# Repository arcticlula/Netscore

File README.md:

# Netscore
Device that keeps track of a volleyball's game score (points and sets). 

Ideally it should be mounted on the net, since it has a display on the front and back and buttons on the sides.

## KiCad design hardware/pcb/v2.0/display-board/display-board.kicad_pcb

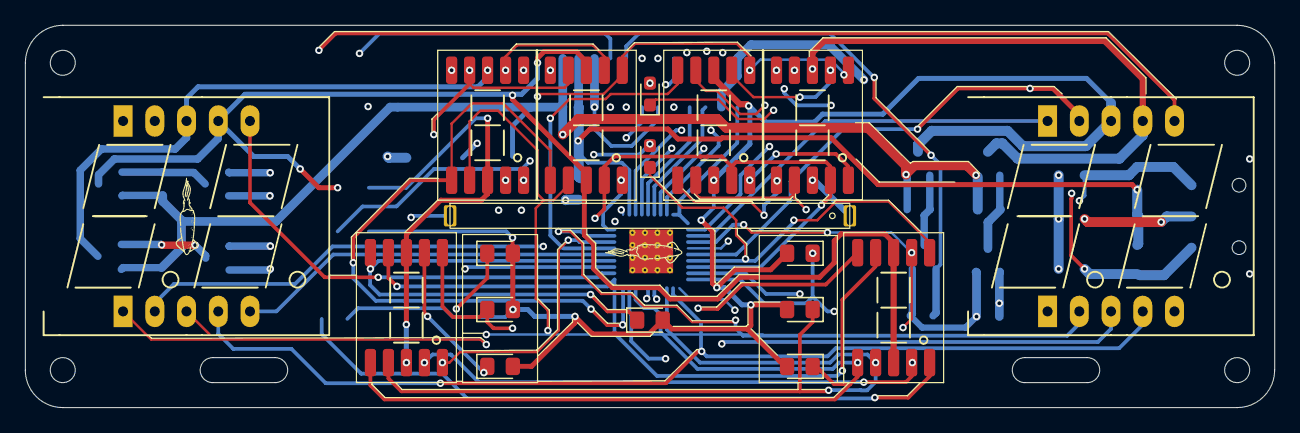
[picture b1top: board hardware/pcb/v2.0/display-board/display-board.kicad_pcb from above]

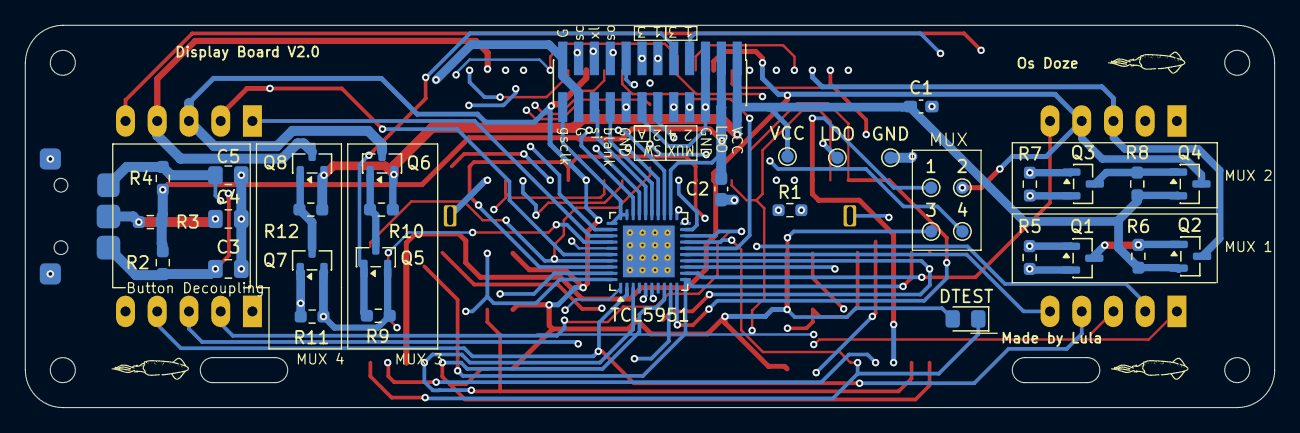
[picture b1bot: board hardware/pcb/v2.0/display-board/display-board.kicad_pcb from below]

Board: 4 copper layers, 100.0 x 30.6 mm, 58 parts (36 on the bottom side), 51 nets.

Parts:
1, 2, 3, 4: TestPoint; TestPoint_Pad_D1.0mm
A1: Conn_02x12_Odd_Even; PinHeader_2x12_P1.27mm_Vertical_SMD
C1: 10uF; C_0603_1608Metric_Pad1.08x0.95mm_HandSolder
C2: 0.1uF; C_0603_1608Metric_Pad1.08x0.95mm_HandSolder
C3, C4, C5: 2.2uF; C_0805_2012Metric_Pad1.18x1.45mm_HandSolder
D1: LED; LED Bar
D3, D4, D5, D6, D7, D8, D9: LED; LED_0805_2012Metric_Pad1.15x1.40mm_HandSolder
D10, D11: LED; LED_0603_1608Metric_Pad1.05x0.95mm_HandSolder
DTEST: LED; LED_0805_2012Metric_Pad1.15x1.40mm_HandSolder
GND: TestPoint; TestPoint_Pad_D1.0mm
H1, H2, H3, H4: MountingHole; MountingHole_2mm
LDO: TestPoint; TestPoint_Pad_D1.0mm
Q1, Q3, Q5, Q7: AO3400A; SOT-23
Q2, Q4, Q6, Q8: AO3401A; SOT-23
R1: 651; R_0603_1608Metric_Pad0.98x0.95mm_HandSolder
R2, R3, R4: 100k; R_0603_1608Metric_Pad0.98x0.95mm_HandSolder
R5, R6, R7, R8, R9, R10, R11, R12: 10K; R_0603_1608Metric_Pad0.98x0.95mm_HandSolder
SW1: Thumbwheel
TCL5951: TLC5951RHA; Texas_RHA0040B_VQFN-40-1EP_6x6mm_P0.5mm_EP4.15x4.15mm_Therm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
U2, U4, U5, U6, U7, U9: GS-S2011AB; GS-2011AB
U3, U8: 7Seg 2Dig 0.56in; 7Seg 0.56In Double
VCC: TestPoint; TestPoint_Pad_D1.0mm

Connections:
/7SEG_MUX_1: 1.1, Q2.3 (D), U2.3 (CA), U2.8 (CA), U3.8 (CA_D1), U4.3 (CA), U4.8 (CA)
/7SEG_MUX_2: 2.1, Q4.3 (D), U3.7 (CA_D2), U5.3 (CA), U5.8 (CA), U6.3 (CA), U6.8 (CA)
/7SEG_MUX_3: 3.1, D3.2 (A), D4.2 (A), D5.2 (A), D6.2 (A), D7.2 (A), D8.2 (A), D9.2 (A), DTEST.2 (A), Q6.3 (D), U7.3 (CA), U7.8 (CA), U8.8 (CA_D1)
/7SEG_MUX_4: 4.1, D1.2 (A), D10.2 (A), D11.2 (A), Q8.3 (D), U8.7 (CA_D2), U9.3 (CA), U9.8 (CA)
/BLANK: A1.17, TCL5951.23 (XBLNK)
/DCSIN: A1.18, TCL5951.25 (DCSIN)
/DCSOUT: A1.16, TCL5951.6 (DCSOUT)
/GSCLK: A1.24, TCL5951.29 (GSCKG), TCL5951.30 (GSCKR), TCL5951.31 (GSCKB)
/GSLAT: A1.19, TCL5951.28 (GSLAT)
/GSSIN: A1.20, TCL5951.26 (GSSIN)
/GSSOUT: A1.15, TCL5951.5 (GSSOUT)
/LDO_CTRL: A1.3, A1.4, C2.1, LDO.1, R2.1, R3.1, R4.1, TCL5951.22 (VCC)
/MUX_1: A1.7, Q1.1 (G), R5.1
/MUX_2: A1.8, Q3.1 (G), R7.1
/MUX_3: A1.9, Q5.1 (G), R9.1
/MUX_4: A1.10, Q7.1 (G), R11.1
/OUTB0: D5.1 (K), D10.1 (K), TCL5951.34 (OUTB0), U4.7 (A), U6.7 (A)
/OUTB1: D4.1 (K), D11.1 (K), TCL5951.37 (OUTB1), U4.6 (B), U6.6 (B)
/OUTB2: D1.1 (K), D7.1 (K), TCL5951.40 (OUTB2), U4.4 (C), U6.4 (C)
/OUTB3: D8.1 (K), TCL5951.3 (OUTB3), U4.2 (D), U6.2 (D)
/OUTB4: D9.1 (K), TCL5951.8 (OUTB4), U4.1 (E), U6.1 (E)
/OUTB5: D3.1 (K), TCL5951.11 (OUTB5), U4.9 (F), U6.9 (F)
/OUTB6: D6.1 (K), TCL5951.14 (OUTB6), U4.10 (G), U6.10 (G)
/OUTB7: DTEST.1 (K), TCL5951.17 (OUTB7), U4.5 (DP), U6.5 (DP)
/OUTG0: TCL5951.32 (OUTG0), U2.7 (A), U5.7 (A), U7.7 (A), U9.7 (A)
/OUTG1: TCL5951.35 (OUTG1), U2.6 (B), U5.6 (B), U7.6 (B), U9.6 (B)
/OUTG2: TCL5951.38 (OUTG2), U2.4 (C), U5.4 (C), U7.4 (C), U9.4 (C)
/OUTG3: TCL5951.1 (OUTG3), U2.2 (D), U5.2 (D), U7.2 (D), U9.2 (D)
/OUTG4: TCL5951.10 (OUTG4), U2.1 (E), U5.1 (E), U7.1 (E), U9.1 (E)
/OUTG5: TCL5951.13 (OUTG5), U2.9 (F), U5.9 (F), U7.9 (F), U9.9 (F)
/OUTG6: TCL5951.16 (OUTG6), U2.10 (G), U5.10 (G), U7.10 (G), U9.10 (G)
/OUTG7: TCL5951.19 (OUTG7), U2.5 (DP), U5.5 (DP), U7.5 (DP), U9.5 (DP)
/OUTR0: TCL5951.33 (OUTR0), U3.10 (a), U8.10 (a)
/OUTR1: TCL5951.36 (OUTR1), U3.9 (b), U8.9 (b)
/OUTR2: TCL5951.39 (OUTR2), U3.1 (c), U8.1 (c)
/OUTR3: TCL5951.2 (OUTR3), U3.4 (d), U8.4 (d)
/OUTR4: TCL5951.9 (OUTR4), U3.3 (e), U8.3 (e)
/OUTR5: TCL5951.12 (OUTR5), U3.6 (f), U8.6 (f)
/OUTR6: TCL5951.15 (OUTR6), U3.5 (g), U8.5 (g)
/OUTR7: TCL5951.18 (OUTR7), U3.2 (DP), U8.2 (DP)
/SCLK: A1.21, TCL5951.24 (DCSCK), TCL5951.27 (GSSCK)
/SW_1: A1.11, C3.1, R2.2, SW1.1
/SW_2: A1.12, C4.1, R3.2, SW1.T
/SW_3: A1.13, C5.1, R4.2, SW1.2
/VCC_CTRL: A1.1, A1.2, C1.1, Q2.2 (S), Q4.2 (S), Q6.2 (S), Q8.2 (S), R6.1, R8.1, R10.1, R12.1, VCC.1
GND: A1.5, A1.6, A1.14, A1.22, A1.23, C1.2, C2.2, C3.2, C4.2, C5.2, GND.1, Q1.2 (S), Q3.2 (S), Q5.2 (S), Q7.2 (S), R1.2, R5.2, R7.2, R9.2, R11.2, SW1.C, TCL5951.20 (GND), TCL5951.41 (GND)
unnamed: Q1.3 (D), Q2.1 (G), R6.2
unnamed: Q3.3 (D), Q4.1 (G), R8.2
unnamed: Q5.3 (D), Q6.1 (G), R10.2
unnamed: Q7.3 (D), Q8.1 (G), R12.2
unnamed: R1.1, TCL5951.21 (IREF)

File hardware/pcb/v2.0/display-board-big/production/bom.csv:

Designator,Footprint,Quantity,Value,LCSC Part #
"1, 2, 3, 4, GND, LDO, VCC",TestPoint_Pad_D1.0mm,7,TestPoint,
A1,PinHeader_2x12_P1.27mm_Vertical_SMD,1,Conn_02x12_Odd_Even,
C1,0603,1,10uF,
C2,0603,1,0.1uF,
"C3, C4, C5",0805,3,2.2uF,
"D1, D13, D14, D6",LED Bar,4,BAR LED,
"D10, D3, D4, D5, D7, D8, D9, DT1, DT2, DT3",0805,10,LED,
"D11, D12",0603,2,LED,
"Q1, Q3, Q5, Q7",SOT-23,4,AO3400A,
"Q2, Q4, Q6, Q8",SOT-23,4,AO3401A,
R1,0603,1,651,
"R10, R11, R12, R5, R6, R7, R8, R9",0603,8,10K,
"R2, R3, R4",0603,3,100k,
SW1,Thumbwheel,1,~,
U1,Texas_RHA0040B_VQFN-40-1EP_6x6mm_P0.5mm_EP4.15x4.15mm_ThermalVias,1,TLC5951RHA,
"U10, U3, U5, U6, U7, U8",GS-2011AB,6,GS-S2011AB,
"U11, U2, U4, U9",7Seg SMD 0.8in Single,4,SMD 0.8in,

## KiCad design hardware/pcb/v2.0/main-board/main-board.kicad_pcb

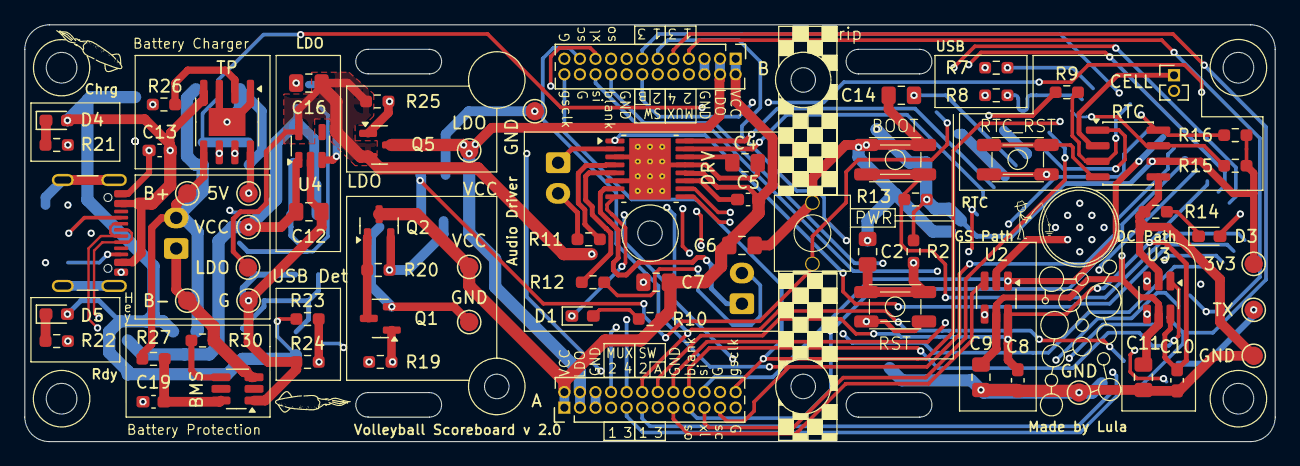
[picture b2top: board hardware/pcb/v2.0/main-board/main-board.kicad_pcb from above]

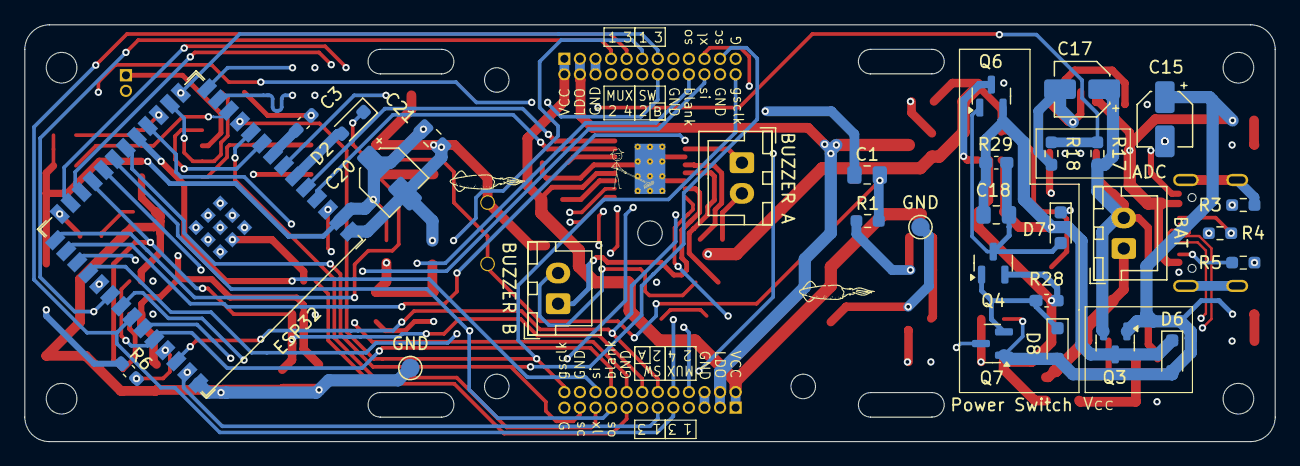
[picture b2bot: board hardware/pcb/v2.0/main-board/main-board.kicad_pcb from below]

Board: 4 copper layers, 102.0 x 34.0 mm, 109 parts (30 on the bottom side), 80 nets.

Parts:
3v3, 5V: TestPoint_Alt; TestPoint_Pad_D1.5mm
A: Conn_02x12_Odd_Even; PinHeader_2x12_P1.27mm_Vertical
B: Conn_02x12_Odd_Even; PinHeader_2x12_P1.27mm_Vertical
B+: TestPoint_Alt; TestPoint_Pad_D1.5mm
B-: TestPoint_Alt; TestPoint_Pad_D1.5mm
BAT: Conn_01x02_Pin; JST_XH_B2B-XH-A_1x02_P2.50mm_Vertical
BMS: FS312MH; SOT-23-6_Handsoldering
BOOT: SW_Push; Button_3x4x2.5
BUZZER A: Conn_01x02_Pin; JST_XH_B2B-XH-A_1x02_P2.50mm_Vertical
BUZZER B: Conn_01x02_Pin; JST_XH_B2B-XH-A_1x02_P2.50mm_Vertical
C1, C2: 100nF; C_0805_2012Metric_Pad1.18x1.45mm_HandSolder
C3, C8, C10: 1nF; C_0603_1608Metric_Pad1.08x0.95mm_HandSolder
C4: 2.2uF; C_0805_2012Metric_Pad1.18x1.45mm_HandSolder
C5: 10nF; C_0603_1608Metric_Pad1.08x0.95mm_HandSolder
C6: 10uF; C_0805_2012Metric_Pad1.18x1.45mm_HandSolder
C7, C9, C11, C14, C18, C21: 0.1uF; C_0805_2012Metric_Pad1.18x1.45mm_HandSolder
C12, C16: 1uF; C_0805_2012Metric_Pad1.18x1.45mm_HandSolder
C13, C19: 100nF; C_0603_1608Metric_Pad1.08x0.95mm_HandSolder
C15, C17, C20: 10uF; CP_Elec_4x5.3
CELL: Conn_01x02_Pin; PinHeader_1x02_P1.27mm_Vertical
D1, D3, D4, D5: LED; LED_0603_1608Metric_Pad1.05x0.95mm_HandSolder
D2, D6, D7, D8: BAT20J; D_SOD-323_HandSoldering
DRV: DRV8833PWP; HTSSOP-16-1EP_4.4x5mm_P0.65mm_EP3.4x5mm_Mask2.46x2.31mm_The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
ESP32: ESP32-S3-WROOM-1; ESP32-S3-WROOM-1U
G: TestPoint_Alt; TestPoint_Pad_D1.5mm
GND: TestPoint_Alt; TestPoint_Pad_D1.5mm
GND#2, GND#3, GND#4, GND#5, GND#6: TestPoint_Alt; TestPoint_Pad_D1.5mm
H1, H2, H3, H4, H5, H6, H7, H8: MountingHole; MountingHole_2mm
J1: USB_C_Receptacle_USB2.0_16P; USB_C_Receptacle_GCT_USB4105-xx-A_16P_TopMnt_Horizontal
LDO: TestPoint_Alt; TestPoint_Pad_D1.5mm
LDO#2: TestPoint_Alt; TestPoint_Pad_D1.5mm
PWR: SW_Push; Kahil Mute 6.2x6.2x7.3
Q1, Q4: AO3400A; SOT-23
Q2, Q3, Q5, Q6, Q7: AO3401A; SOT-23
R1, R2, R13: 10k; R_0603_1608Metric_Pad0.98x0.95mm_HandSolder
R3, R7, R8: 0; R_0603_1608Metric_Pad0.98x0.95mm_HandSolder
R4, R5: 5.1K; R_0603_1608Metric_Pad0.98x0.95mm_HandSolder
R6: 499; C_0603_1608Metric_Pad1.08x0.95mm_HandSolder
R9, R17, R18, R19, R20, R24, R25: 100k; R_0603_1608Metric_Pad0.98x0.95mm_HandSolder
R10, R14, R21, R22: 2.2K; R_0603_1608Metric_Pad0.98x0.95mm_HandSolder
R11, R12: 300; R_0603_1608Metric_Pad0.98x0.95mm_HandSolder
R15, R16: 4.7k; R_0603_1608Metric_Pad0.98x0.95mm_HandSolder
R23: 56k; R_0603_1608Metric_Pad0.98x0.95mm_HandSolder
R26: R; R_0603_1608Metric_Pad0.98x0.95mm_HandSolder
R27: 100; R_0603_1608Metric_Pad0.98x0.95mm_HandSolder
R28, R29: 100k; C_0603_1608Metric_Pad1.08x0.95mm_HandSolder
R30: 2K; R_0603_1608Metric_Pad0.98x0.95mm_HandSolder
RST: SW_Push; Button_3x4x2.5
RTC: DS3231MZ; SOIC-8_3.9x4.9mm_P1.27mm
RTC_RST: SW_Push; Button_3x4x2.5
TP: TP4056; SOIC-8-1EP_3.9x4.9mm_P1.27mm_EP2.29x3mm
TX: TestPoint_Alt; TestPoint_Pad_D1.5mm
U2, U3: 74LVC1G3157; SOT-23-6_Handsoldering
U4: AP2112K-3.3; SOT-23-5
VCC: TestPoint_Alt; TestPoint_Pad_D1.5mm
VCC#2: TestPoint_Alt; TestPoint_Pad_D1.5mm

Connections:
+BATT: B+.1, BAT.2, C17.1, Q3.2 (S), R17.1, R27.1, TP.5 (BAT)
-BATT: B-.1, BAT.1, BMS.3 (BAT-), R30.1
/ADC_BAT: C14.2, ESP32.7 (GPIO7/TOUCH7/ADC1_CH6), R17.2, R18.1
/BLANK: A.17, B.17, ESP32.21 (GPIO13/TOUCH13/ADC2_CH2/FSPIQ/FSPIIO7/S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)
/BUZZER_A_+: BUZZER A.1, DRV.2 (AOUT1)
/BUZZER_A_-: BUZZER A.2, R11.2
/BUZZER_B_+: BUZZER B.1, DRV.7 (BOUT1)
/BUZZER_B_-: BUZZER B.2, R12.2
/BZ_A_1: DRV.16 (AIN1), ESP32.5 (GPIO5/TOUCH5/ADC1_CH4)
/BZ_A_2: DRV.15 (AIN2), ESP32.4 (GPIO4/TOUCH4/ADC1_CH3)
/BZ_B_1: DRV.9 (BIN1), ESP32.24 (GPIO47/SPICLK_P/SUBSPICLK_P_DIFF)
/BZ_B_2: DRV.10 (BIN2), ESP32.25 (GPIO48/SPICLK_N/SUBSPICLK_N_DIFF)
/DCSIN: A.18, ESP32.36 (U0RXD/GPIO44/CLK_OUT2), U3.1
/DCSIN_B: B.18, U3.4
/DCSOUT_A: A.16, U3.3
/DRV_~SLEEP: DRV.1 (~SLEEP), ESP32.28 (SPIIO6/GPIO35/FSPID/SUBSPID)
/EN: C2.1, ESP32.3 (EN), R2.2, RST.1
/GSCLK: A.24, B.24, ESP32.11 (GPIO18/U1RXD/ADC2_CH7/CLK_OUT3)
/GSLAT: A.19, B.19, ESP32.10 (GPIO17/U1TXD/ADC2_CH6)
/GSSIN: A.20, ESP32.19 (GPIO11/TOUCH11/ADC2_CH0/FSPID/FSPIIO5/S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), U2.1
/GSSIN_B: B.20, U2.4
/GSSOUT_A: A.15, U2.3
/LDO_CTRL_EN: ESP32.29 (SPIIO7/GPIO36/FSPICLK/SUBSPICLK), Q5.1 (G), R25.2
/LDO_EN: Q6.3 (D), U4.3 (EN)
/LDO_LATCH: ESP32.18 (GPIO10/TOUCH10/ADC1_CH9/FSPICS0/FSPIIO4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), Q7.3 (D)
/MUX_1: A.7, B.7, ESP32.32 (MTCK/GPIO39/CLK_OUT3/SUBSPICS1)
/MUX_2: A.8, B.8, ESP32.33 (MTDO/GPIO40/CLK_OUT2)
/MUX_3: A.9, B.9, ESP32.34 (MTDI/GPIO41/CLK_OUT1)
/MUX_4: A.10, B.10, ESP32.35 (MTMS/GPIO42)
/RTC_BAT_+: CELL.1, RTC.2 (VCC)
/RTC_CLK: ESP32.9 (GPIO16/U0CTS/ADC2_CH5/XTAL_32K_N), RTC.1 (32KHZ)
/RTC_SCL: ESP32.17 (GPIO9/TOUCH9/ADC1_CH8/FSPIHD/SUBSPIHD), R16.1, RTC.8 (SCL)
/RTC_SDA: ESP32.12 (GPIO8/TOUCH8/ADC1_CH7/SUBSPICS1), R15.1, RTC.7 (SDA)
/RTC_~INT: ESP32.16 (GPIO46), R9.1, RTC.3 (~INT/SQW)
/SCLK: A.21, B.21, ESP32.20 (GPIO12/TOUCH12/ADC2_CH1/FSPICLK/FSPIIO6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)
/SLOT_A_DET: A.14, C8.1, C10.1, ESP32.23 (GPIO21), U2.6, U3.6
/SLOT_B_DET: B.14, ESP32.31 (GPIO38/FSPIWP/SUBSPIWP)
/SW_1: A.11, B.11, ESP32.39 (GPIO1/TOUCH1/ADC1_CH0)
/SW_2: A.12, B.12, ESP32.38 (GPIO2/TOUCH2/ADC1_CH1)
/SW_3: A.13, B.13, ESP32.15 (GPIO3/TOUCH3/ADC1_CH2)
/SW_PWR: C1.1, D2.1 (K), D7.1 (K), PWR.1, R1.2
/U0TXD: R6.2, TX.1
/USB_D+: J1.A6 (D+), J1.B6 (D+), R7.2
/USB_D-: J1.A7 (D-), J1.B7 (D-), R8.2
/VBUS_DET: ESP32.22 (GPIO14/TOUCH14/ADC2_CH3/FSPIWP/FSPIDQS/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), R23.2, R24.1
/VCC_CTRL_EN: ESP32.30 (SPIDQS/GPIO37/FSPIQ/SUBSPIQ), Q1.1 (G), R19.1
GND: A.5, A.6, A.22, A.23, B.5, B.6, B.22, B.23, BMS.1 (GND), BOOT.1, C1.2, C2.2, C3.1, C4.1, C6.1, C7.1, C8.2, C9.1, C10.2, C11.1, C12.2, C13.2, C14.1, C15.2, C16.2, C17.2, C19.2, C20.2, C21.1, CELL.2, DRV.3 (AISEN), DRV.6 (BISEN), DRV.13 (GND), DRV.17 (GND), ESP32.1 (GND), ESP32.40 (GND), ESP32.41 (GND), G.1, GND.1, GND#2.1, GND#3.1, GND#4.1, GND#5.1, GND#6.1, J1.A1 (GND), J1.A12 (GND), J1.B1 (GND), J1.B12 (GND), PWR.2, Q1.2 (S), Q4.2 (S), R3.1, R4.1, R5.1, R9.2, R14.2, R18.2, R19.2, R24.2, R26.2, R28.2, RST.2, RTC.5 (GND), RTC_RST.1, TP.1 (TEMP), TP.3 (GND), TP.9 (PP), U2.2 (GND), U3.2 (GND), U4.2 (GND)
LDO: 3v3.1, C16.1, C20.1, C21.2, ESP32.2 (3V3), LDO.1, Q5.2 (S), R2.1, R13.1, R15.2, R16.2, R25.1, RTC.6 (VBAT), U4.5 (VOUT)
LDO_CTRL: A.3, A.4, B.3, B.4, C9.2, C11.2, LDO#2.1, Q5.3 (D), U2.5 (VCC), U3.5 (VCC)
unnamed: BMS.4 (CS), R30.2
unnamed: BMS.6 (VCC), C19.1, R27.2
unnamed: D1.2 (A), R10.2
unnamed: D1.1 (K), DRV.8 (~FAULT)
unnamed: D2.2 (A), ESP32.6 (GPIO6/TOUCH6/ADC1_CH5)
unnamed: D3.2 (A), ESP32.26 (GPIO45)
unnamed: D3.1 (K), R14.1
unnamed: D4.1 (K), R21.1
unnamed: D5.1 (K), R22.1
unnamed: C18.2, D7.2 (A), Q4.3 (D), Q6.1 (G), R29.2
unnamed: D8.1 (K), Q4.1 (G), Q7.2 (S), R28.1
unnamed: DRV.4 (AOUT2), R11.1
unnamed: DRV.5 (BOUT2), R12.1
unnamed: C5.1, DRV.11 (VCP)
unnamed: C4.2, DRV.14 (VINT)
unnamed: J1.A5 (CC1), R4.2
unnamed: J1.B5 (CC2), R5.2
unnamed: J1.S1 (SHIELD), R3.2
unnamed: Q1.3 (D), Q2.1 (G), R20.2
unnamed: RTC.4 (~RST), RTC_RST.2
unnamed: R26.1, TP.2 (PROG)
unnamed: R21.2, TP.7 (~CHRG)
unnamed: R22.2, TP.6 (~STDBY)
unnamed: BOOT.2, ESP32.27 (GPIO0/BOOT), R13.2
unnamed: C3.2, ESP32.8 (GPIO15/U0RTS/ADC2_CH4/XTAL_32K_P)
unnamed: ESP32.13 (GPIO19/U1RTS/ADC2_CH8/CLK_OUT2/USB_D-), R8.1
unnamed: ESP32.14 (GPIO20/U1CTS/ADC2_CH9/CLK_OUT1/USB_D+), R7.1
unnamed: ESP32.37 (U0TXD/GPIO43/CLK_OUT1), R6.1
VBUS: 5V.1, C13.1, C15.1, D4.2 (A), D5.2 (A), D6.2 (A), D8.2 (A), J1.A4 (VBUS), J1.A9 (VBUS), J1.B4 (VBUS), J1.B9 (VBUS), Q3.1 (G), Q7.1 (G), R23.1, TP.4 (VCC), TP.8 (CE)
VCC: C12.1, C18.1, D6.1 (K), Q2.2 (S), Q3.3 (D), Q6.2 (S), R1.1, R20.1, R29.1, U4.1 (VIN), VCC#2.1
VCC_CTRL: A.1, A.2, B.1, B.2, C5.2, C6.2, C7.2, DRV.12 (VM), Q2.3 (D), R10.1, VCC.1

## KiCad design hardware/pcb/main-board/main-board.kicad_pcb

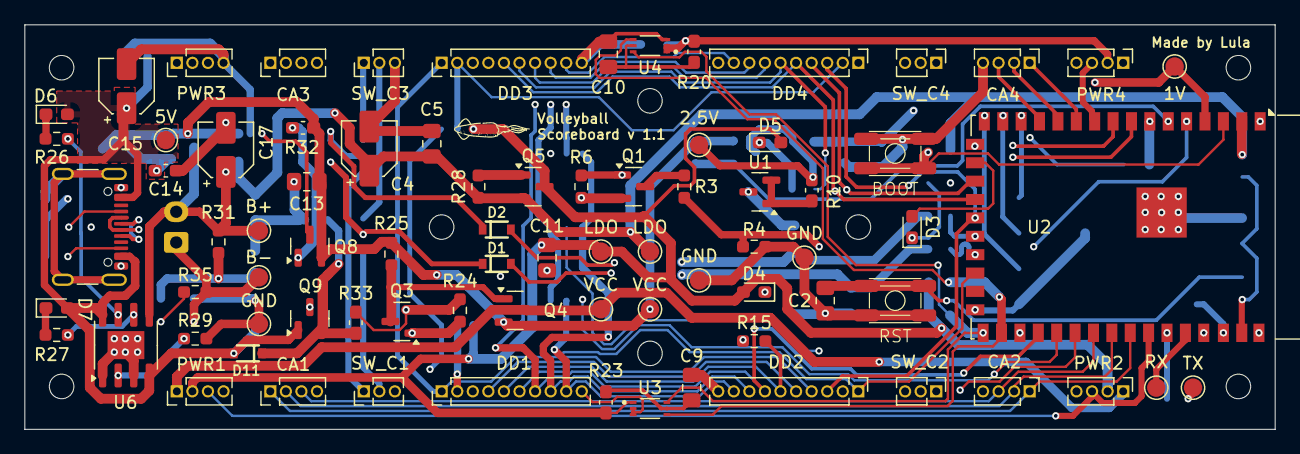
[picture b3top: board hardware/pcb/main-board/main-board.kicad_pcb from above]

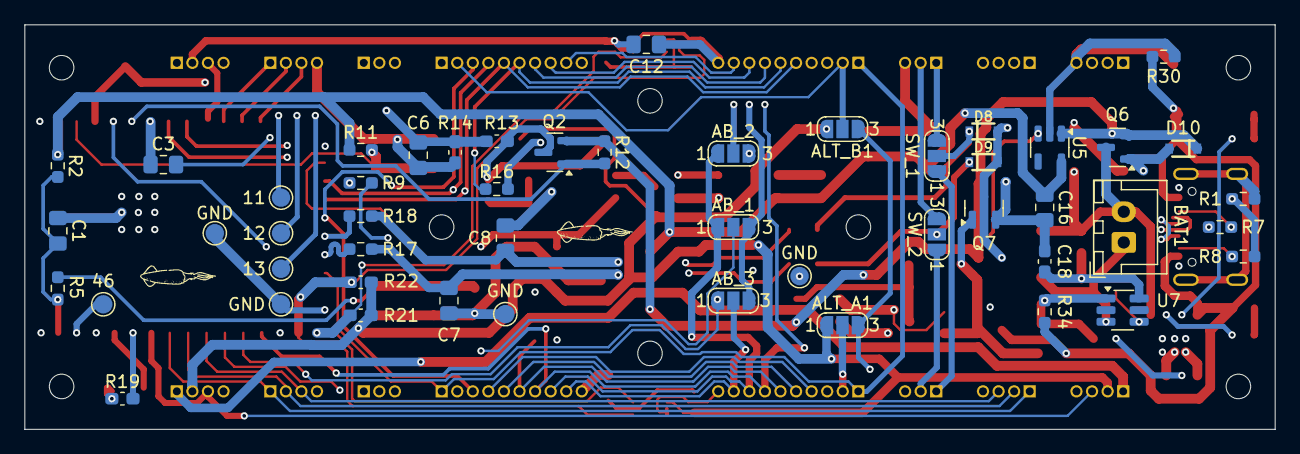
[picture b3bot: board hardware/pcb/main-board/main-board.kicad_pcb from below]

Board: 4 copper layers, 102.0 x 33.0 mm, 137 parts (50 on the bottom side), 87 nets.

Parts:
1V, 2.5V, 5V, 11, 12, 13, 46: TestPoint_Alt; TestPoint_Pad_D1.5mm
AB_1, AB_2, AB_3: SolderJumper_3_Open; SolderJumper-3_P1.3mm_Open_RoundedPad1.0x1.5mm_NumberLabels
ALT_A1: SolderJumper_3_Open; SolderJumper-3_P1.3mm_Open_RoundedPad1.0x1.5mm_NumberLabels
ALT_B1: SolderJumper_3_Open; SolderJumper-3_P1.3mm_Open_RoundedPad1.0x1.5mm_NumberLabels
B+: TestPoint_Alt; TestPoint_Pad_D1.5mm
B-: TestPoint_Alt; TestPoint_Pad_D1.5mm
BAT1: Conn_01x02_Pin; JST_XH_B2B-XH-A_1x02_P2.50mm_Vertical
BOOT: SW_Push; Button_3x4x2.5
C1, C13, C16: 1uF; C_0805_2012Metric_Pad1.18x1.45mm_HandSolder
C2, C3, C5, C6, C9, C10, C11, C12: 0.1uF; C_0805_2012Metric_Pad1.18x1.45mm_HandSolder
C4, C15, C17: 10uF; CP_Elec_4x5.3
C7, C8: C; C_0805_2012Metric_Pad1.18x1.45mm_HandSolder
C14, C18: 100nF; C_0603_1608Metric_Pad1.08x0.95mm_HandSolder
CA1, CA2, CA3, CA4: Conn_01x04_Pin; PinHeader_1x04_P1.27mm_Vertical
D1, D2, D10: BAT20JFILM; SOD-323
D3, D4, D5, D6, D7: LED; LED_0603_1608Metric_Pad1.05x0.95mm_HandSolder
D8, D9, D11: BAT20J; SOD-323
DD1, DD2, DD3, DD4: Conn_01x10_Pin; PinHeader_1x10_P1.27mm_Vertical
GND: TestPoint_Alt; TestPoint_Pad_D1.5mm
GND#2, GND#3, GND#4, GND#5, GND#6, GND#7: TestPoint_Alt; TestPoint_Pad_D1.5mm
H1, H2, H3, H4, H5, H6, H7, H8: MountingHole; MountingHole_2mm
J1: USB_C_Receptacle_USB2.0_16P; USB_C_Receptacle_GCT_USB4105-xx-A_16P_TopMnt_Horizontal
LDO: TestPoint_Alt; TestPoint_Pad_D1.5mm
LDO#2: TestPoint_Alt; TestPoint_Pad_D1.5mm
PWR1, PWR2, PWR3, PWR4: Conn_01x04_Pin; PinHeader_1x04_P1.27mm_Vertical
Q1, Q2, Q4, Q5, Q6, Q8, Q9: AO3401A; SOT-23
Q3, Q7: AO3400A; SOT-23
R1, R5, R17, R18: 0; R_0603_1608Metric_Pad0.98x0.95mm_HandSolder
R2, R6, R11: 10k; R_0603_1608Metric_Pad0.98x0.95mm_HandSolder
R3, R4, R29: R; R_0603_1608Metric_Pad0.98x0.95mm_HandSolder
R7, R8: 5.1K; R_0603_1608Metric_Pad0.98x0.95mm_HandSolder
R9, R15, R16, R26, R27: 2.2K; R_0603_1608Metric_Pad0.98x0.95mm_HandSolder
R10, R13, R14: R; C_0603_1608Metric_Pad1.08x0.95mm_HandSolder
R12, R24, R25, R28, R34: 1M; R_0603_1608Metric_Pad0.98x0.95mm_HandSolder
R19: 499; C_0603_1608Metric_Pad1.08x0.95mm_HandSolder
R20, R23: 1k; C_0603_1608Metric_Pad1.08x0.95mm_HandSolder
R21, R22: 4.7k; C_0603_1608Metric_Pad1.08x0.95mm_HandSolder
R30: 10K; R_0603_1608Metric_Pad0.98x0.95mm_HandSolder
R31: 100; R_0603_1608Metric_Pad0.98x0.95mm_HandSolder
R32, R33: 1M; C_0603_1608Metric_Pad1.08x0.95mm_HandSolder
R35: 2K; R_0603_1608Metric_Pad0.98x0.95mm_HandSolder
RST: SW_Push; Button_3x4x2.5
RX: TestPoint_Alt; TestPoint_Pad_D1.5mm
SW_1, SW_2: SolderJumper_3_Open; SolderJumper-3_P1.3mm_Open_RoundedPad1.0x1.5mm_NumberLabels
SW_C1, SW_C2, SW_C3, SW_C4: Conn_01x03_Pin; PinHeader_1x03_P1.27mm_Vertical
TX: TestPoint_Alt; TestPoint_Pad_D1.5mm
U1: TL431DBZ; SOT-23
U2: ESP32-S2-WROVER-I; ESP32-S2-WROVER
U3, U4: BH1750FVI-TR; XDCR_BH1750FVI-TR
U5: AP2112K-3.3; SOT-23-5
U6: TP4056; SOIC-8-1EP_3.9x4.9mm_P1.27mm_EP2.29x3mm
U7: FS312MH; SOT-23-6_Handsoldering
VCC: TestPoint_Alt; TestPoint_Pad_D1.5mm
VCC#2: TestPoint_Alt; TestPoint_Pad_D1.5mm

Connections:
+BATT: B+.1, BAT1.2, C17.1, Q1.2 (S), Q6.3 (D), R6.1, R31.1, U6.5 (BAT)
-BATT: B-.1, BAT1.1, R35.1, U7.3 (BAT-)
/1V: 1V.1, C6.1, R13.2, R14.2, U2.4 (IO01)
/2.5V: 2.5V.1, Q2.3 (D), R10.1, R13.1
/ADC_BAT_EN: C3.1, U2.7 (IO04)
/ADC_BAT_V: R3.2, R4.1, U2.5 (IO02)
/ADC_VREF_EN: Q2.1 (G), R12.2, U2.6 (IO03)
/ALT_A: ALT_A1.2 (C), DD1.2, DD2.2
/ALT_B: ALT_B1.2 (C), DD3.2, DD4.2
/BLANK: DD1.4, DD2.4, DD3.4, DD4.4, U2.19 (IO16)
/BUZZER_A: PWR1.3, PWR2.3, U2.36 (IO42)
/BUZZER_B: PWR3.3, PWR4.3, U2.10 (IO07)
/CTRL: ALT_A1.3 (B), ALT_B1.3 (B), U2.32 (IO38)
/EN: C1.1, R2.2, R5.1, U2.41 (EN)
/GPIO11: 11.1, U2.14 (IO11)
/GPIO12: 12.1, U2.15 (IO12)
/GPIO13: 13.1, U2.16 (IO13)
/GPIO46: 46.1, U2.40 (IO46)
/GSCLK: DD1.3, DD2.3, DD3.3, DD4.3, U2.21 (IO18)
/LDO_CTRL_EN: Q5.1 (G), R28.2
/LDO_EN: Q8.3 (D), U5.3 (EN)
/LDO_LATCH: Q9.3 (D), U2.39 (IO45)
/MC_DD_1_A: CA1.1, CA2.1, U2.35 (IO41)
/MC_DD_1_B: CA3.1, CA4.1, U2.11 (IO08)
/MC_DD_2_A: CA1.2, CA2.2, U2.34 (IO40)
/MC_DD_2_B: CA3.2, CA4.2, U2.12 (IO09)
/MC_SD_A: CA1.3, CA2.3, U2.33 (IO39)
/MC_SD_B: CA3.3, CA4.3, U2.13 (IO10)
/MISO(SOUT): AB_2.3 (B), AB_3.1 (A), U2.31 (IO37)
/MOSI(SIN): AB_1.2 (C), U2.29 (IO35)
/SCL: R21.1, U2.27 (IO33), U3.6 (SCL), U4.6 (SCL)
/SCLK: DD1.7, DD2.7, DD3.7, DD4.7, U2.30 (IO36)
/SDA: R22.1, U2.28 (IO34), U3.4 (SDA), U4.4 (SDA)
/SIN_A: AB_1.1 (A), AB_2.1 (A), DD1.8, DD2.8
/SIN_B: AB_1.3 (B), AB_3.3 (B), DD3.8, DD4.8
/SOUT_A: AB_3.2 (C), DD1.9, DD2.9
/SOUT_B: AB_2.2 (C), DD3.9, DD4.9
/SW1: D2.C, D8.C, SW_1.2 (C)
/SW1_A: SW_1.1 (A), SW_C1.1, SW_C2.1
/SW1_B: SW_1.3 (B), SW_C3.1, SW_C4.1
/SW2: D1.C, D9.C, SW_2.2 (C)
/SW2_A: SW_2.1 (A), SW_C1.2, SW_C2.2
/SW2_B: SW_2.3 (B), SW_C3.2, SW_C4.2
/U0RXD: RX.1, U2.38 (RXD0)
/U0TXD: R19.2, TX.1
/USB_D+: C8.1, J1.A6 (D+), J1.B6 (D+), R18.2
/USB_D-: C7.1, J1.A7 (D-), J1.B7 (D-), R17.2
/VCC_CTRL: PWR1.1, PWR2.1, PWR3.1, PWR4.1, Q4.3 (D), VCC.1
/VCC_CTRL_EN: Q3.1 (G), R24.1, U2.17 (IO14)
/VPRG: DD1.1, DD2.1, DD3.1, DD4.1, U2.24 (IO21)
/XERR_A: DD1.6, DD2.6, R15.1
/XERR_B: DD3.6, DD4.6, R16.1
/XLAT: DD1.5, DD2.5, DD3.5, DD4.5, U2.20 (IO17)
GND: BOOT.1, C1.2, C2.1, C4.2, C5.1, C6.2, C7.2, C8.2, C9.1, C10.1, C11.1, C12.1, C13.2, C14.2, C15.2, C16.2, C17.2, C18.2, CA1.4, CA2.4, CA3.4, CA4.4, DD1.10, DD2.10, DD3.10, DD4.10, GND.1, GND#2.1, GND#3.1, GND#4.1, GND#5.1, GND#6.1, GND#7.1, J1.A1 (GND), J1.A12 (GND), J1.B1 (GND), J1.B12 (GND), PWR1.4, PWR2.4, PWR3.4, PWR4.4, Q3.2 (S), Q7.2 (S), R1.1, R4.2, R7.1, R8.1, R9.2, R14.1, R24.2, R29.2, R30.2, R33.2, R34.2, RST.2, SW_C1.3, SW_C2.3, SW_C3.3, SW_C4.3, U1.3 (A), U2.1 (GND), U2.26 (GND), U2.42 (GND), U2.43 (GND), U3.2 (ADDR), U3.3 (GND), U4.3 (GND), U5.2 (GND), U6.1 (TEMP), U6.3 (GND), U6.9 (PP), U7.1 (GND)
LDO: C4.1, C5.2, C16.1, LDO#2.1, Q5.2 (S), R2.1, R11.1, R28.1, U2.2 (3V3), U5.5 (VOUT)
LDO_CTRL: ALT_A1.1 (A), ALT_B1.1 (A), C11.2, C12.2, D4.2 (A), D5.2 (A), LDO.1, PWR1.2, PWR2.2, PWR3.2, PWR4.2, Q5.3 (D), R20.2, R21.2, R22.2, R23.2, U3.1 (VCC), U4.1 (VCC), U4.2 (ADDR)
unnamed: C2.2, R5.2, RST.1
unnamed: D3.2 (A), U2.18 (IO15)
unnamed: D3.1 (K), R9.1
unnamed: D4.1 (K), R15.2
unnamed: D5.1 (K), R16.2
unnamed: D6.1 (K), R26.1
unnamed: D7.1 (K), R27.1
unnamed: J1.A5 (CC1), R7.2
unnamed: J1.B5 (CC2), R8.2
unnamed: J1.S1 (SHIELD), R1.2
unnamed: Q1.3 (D), R3.1
unnamed: C3.2, Q1.1 (G), R6.2
unnamed: Q3.3 (D), Q4.1 (G), R25.2
unnamed: D8.A, D9.A, Q7.3 (D), Q8.1 (G), R32.2
unnamed: D11.C, Q7.1 (G), Q9.2 (S), R33.1
unnamed: R10.2, U1.1 (K), U1.2 (REF)
unnamed: BOOT.2, R11.2, U2.3 (IO00)
unnamed: D1.A, U2.8 (IO05)
unnamed: D2.A, U2.9 (IO06)
unnamed: R19.1, U2.37 (TXD0)
unnamed: R17.1, U2.23 (USB_D+)
unnamed: R18.1, U2.22 (USB_D-)
unnamed: C9.2, R23.1, U3.5 (DVI)
unnamed: C10.2, R20.1, U4.5 (DVI)
unnamed: R29.1, U6.2 (PROG)
unnamed: R26.2, U6.7 (~CHRG)
unnamed: R27.2, U6.6 (~STDBY)
unnamed: R35.2, U7.4 (CS)
unnamed: C18.1, R31.2, U7.6 (VCC)
VBUS: 5V.1, C14.1, C15.1, D6.2 (A), D7.2 (A), D10.A, D11.A, J1.A4 (VBUS), J1.A9 (VBUS), J1.B4 (VBUS), J1.B9 (VBUS), Q6.1 (G), Q9.1 (G), R30.1, R34.1, U6.4 (VCC), U6.8 (CE)
VCC: C13.1, D10.C, Q2.2 (S), Q4.2 (S), Q6.2 (S), Q8.2 (S), R12.1, R25.1, R32.1, U5.1 (VIN), VCC#2.1

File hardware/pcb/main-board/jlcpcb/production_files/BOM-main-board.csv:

Comment,Designator,Footprint,LCSC,Quantity
Conn_01x03_Pin,SW_C1,PinHeader_1x03_P1.27mm_Vertical,,1
MountingHole,H3,MountingHole_2mm,,1
MountingHole,H8,MountingHole_2mm,,1
10uF,C4,CP_Elec_4x5.3,,1
MountingHole,H1,MountingHole_2mm,,1
0.1uF,C10,C_0805_2012Metric_Pad1.18x1.45mm_HandSolder,,1
AO3401A,Q4,SOT-23,,1
TP4056,U6,SOIC-8-1EP_3.9x4.9mm_P1.27mm_EP2.29x3mm,,1
MountingHole,H5,MountingHole_2mm,,1
1M,R24,R_0603_1608Metric_Pad0.98x0.95mm_HandSolder,,1
AO3401A,Q8,SOT-23,,1
Conn_01x04_Pin,PWR1,PinHeader_1x04_P1.27mm_Vertical,,1
Conn_01x10_Pin,DD1,PinHeader_1x10_P1.27mm_Vertical,,1
R,R29,R_0603_1608Metric_Pad0.98x0.95mm_HandSolder,,1
LED,D3,LED_0603_1608Metric_Pad1.05x0.95mm_HandSolder,,1
BH1750FVI-TR,U4,XDCR_BH1750FVI-TR,,1
R,R4,R_0603_1608Metric_Pad0.98x0.95mm_HandSolder,,1
1M,R32,C_0603_1608Metric_Pad1.08x0.95mm_HandSolder,,1
MountingHole,H6,MountingHole_2mm,,1
BAT20JFILM,D2,SOD-323,,1
10uF,C17,CP_Elec_4x5.3,,1
0.1uF,C11,C_0805_2012Metric_Pad1.18x1.45mm_HandSolder,,1
R,R10,C_0603_1608Metric_Pad1.08x0.95mm_HandSolder,,1
Conn_01x04_Pin,CA3,PinHeader_1x04_P1.27mm_Vertical,,1
1uF,C13,C_0805_2012Metric_Pad1.18x1.45mm_HandSolder,,1
AO3401A,Q1,SOT-23,,1
1k,R23,C_0603_1608Metric_Pad1.08x0.95mm_HandSolder,,1
1k,R20,C_0603_1608Metric_Pad1.08x0.95mm_HandSolder,,1
1M,R33,C_0603_1608Metric_Pad1.08x0.95mm_HandSolder,,1
LED,D4,LED_0603_1608Metric_Pad1.05x0.95mm_HandSolder,,1
Conn_01x03_Pin,SW_C2,PinHeader_1x03_P1.27mm_Vertical,,1
10uF,C15,CP_Elec_4x5.3,,1
1M,R28,R_0603_1608Metric_Pad0.98x0.95mm_HandSolder,,1
Conn_01x04_Pin,CA1,PinHeader_1x04_P1.27mm_Vertical,,1
0.1uF,C5,C_0805_2012Metric_Pad1.18x1.45mm_HandSolder,,1
MountingHole,H4,MountingHole_2mm,,1
2.2K,R27,R_0603_1608Metric_Pad0.98x0.95mm_HandSolder,,1
AO3401A,Q5,SOT-23,,1
Conn_01x10_Pin,DD4,PinHeader_1x10_P1.27mm_Vertical,,1
0.1uF,C2,C_0805_2012Metric_Pad1.18x1.45mm_HandSolder,,1
LED,D5,LED_0603_1608Metric_Pad1.05x0.95mm_HandSolder,,1
2.2K,R26,R_0603_1608Metric_Pad0.98x0.95mm_HandSolder,,1
Conn_01x10_Pin,DD2,PinHeader_1x10_P1.27mm_Vertical,,1
R,R3,R_0603_1608Metric_Pad0.98x0.95mm_HandSolder,,1
LED,D7,LED_0603_1608Metric_Pad1.05x0.95mm_HandSolder,,1
Conn_01x03_Pin,SW_C4,PinHeader_1x03_P1.27mm_Vertical,,1
Conn_01x04_Pin,PWR2,PinHeader_1x04_P1.27mm_Vertical,,1
AO3401A,Q9,SOT-23,,1
1M,R25,R_0603_1608Metric_Pad0.98x0.95mm_HandSolder,,1
MountingHole,H7,MountingHole_2mm,,1
Conn_01x04_Pin,CA4,PinHeader_1x04_P1.27mm_Vertical,,1
100nF,C14,C_0603_1608Metric_Pad1.08x0.95mm_HandSolder,,1
BAT20JFILM,D1,SOD-323,,1
MountingHole,H2,MountingHole_2mm,,1
BAT20J,D11,SOD-323,,1
Conn_01x03_Pin,SW_C3,PinHeader_1x03_P1.27mm_Vertical,,1
100,R31,R_0603_1608Metric_Pad0.98x0.95mm_HandSolder,,1
2.2K,R15,R_0603_1608Metric_Pad0.98x0.95mm_HandSolder,,1
Conn_01x04_Pin,PWR4,PinHeader_1x04_P1.27mm_Vertical,,1
ESP32-S2-WROVER-I,U2,ESP32-S2-WROVER,,1
Conn_01x04_Pin,PWR3,PinHeader_1x04_P1.27mm_Vertical,,1
USB_C_Receptacle_USB2.0_16P,J1,USB_C_Receptacle_GCT_USB4105-xx-A_16P_TopMnt_Horizontal,,1
0.1uF,C9,C_0805_2012Metric_Pad1.18x1.45mm_HandSolder,,1
AO3400A,Q3,SOT-23,,1
TL431DBZ,U1,SOT-23,,1
Conn_01x10_Pin,DD3,PinHeader_1x10_P1.27mm_Vertical,,1
BH1750FVI-TR,U3,XDCR_BH1750FVI-TR,,1
Conn_01x04_Pin,CA2,PinHeader_1x04_P1.27mm_Vertical,,1
10k,R6,R_0603_1608Metric_Pad0.98x0.95mm_HandSolder,,1
2K,R35,R_0603_1608Metric_Pad0.98x0.95mm_HandSolder,,1
LED,D6,LED_0603_1608Metric_Pad1.05x0.95mm_HandSolder,,1
1uF,C16,C_0805_2012Metric_Pad1.18x1.45mm_HandSolder,,1
2.2K,R9,R_0603_1608Metric_Pad0.98x0.95mm_HandSolder,,1
AP2112K-3.3,U5,SOT-23-5,,1
1uF,C1,C_0805_2012Metric_Pad1.18x1.45mm_HandSolder,,1
SolderJumper_3_Open,SW_2,SolderJumper-3_P1.3mm_Open_RoundedPad1.0x1.5mm_NumberLabels,,1
SolderJumper_3_Open,ALT_A1,SolderJumper-3_P1.3mm_Open_RoundedPad1.0x1.5mm_NumberLabels,,1
1M,R12,R_0603_1608Metric_Pad0.98x0.95mm_HandSolder,,1
0.1uF,C3,C_0805_2012Metric_Pad1.18x1.45mm_HandSolder,,1
FS312MH,U7,SOT-23-6_Handsoldering,,1
BAT20J,D9,SOD-323,,1
AO3400A,Q7,SOT-23,,1
TestPoint_Alt,12,TestPoint_Pad_D1.5mm,,1
BAT20J,D8,SOD-323,,1
499,R19,C_0603_1608Metric_Pad1.08x0.95mm_HandSolder,,1
5.1K,R7,R_0603_1608Metric_Pad0.98x0.95mm_HandSolder,,1
SolderJumper_3_Open,AB_2,SolderJumper-3_P1.3mm_Open_RoundedPad1.0x1.5mm_NumberLabels,,1
0,R17,R_0603_1608Metric_Pad0.98x0.95mm_HandSolder,,1
10k,R2,R_0603_1608Metric_Pad0.98x0.95mm_HandSolder,,1
0.1uF,C12,C_0805_2012Metric_Pad1.18x1.45mm_HandSolder,,1
1M,R34,R_0603_1608Metric_Pad0.98x0.95mm_HandSolder,,1
4.7k,R22,C_0603_1608Metric_Pad1.08x0.95mm_HandSolder,,1
10k,R11,R_0603_1608Metric_Pad0.98x0.95mm_HandSolder,,1
Conn_01x02_Pin,BAT1,JST_XH_B2B-XH-A_1x02_P2.50mm_Vertical,,1
0,R1,R_0603_1608Metric_Pad0.98x0.95mm_HandSolder,,1
0,R5,R_0603_1608Metric_Pad0.98x0.95mm_HandSolder,,1
AO3401A,Q2,SOT-23,,1
R,R14,C_0603_1608Metric_Pad1.08x0.95mm_HandSolder,,1
BAT20JFILM,D10,SOD-323,,1
SolderJumper_3_Open,AB_1,SolderJumper-3_P1.3mm_Open_RoundedPad1.0x1.5mm_NumberLabels,,1
5.1K,R8,R_0603_1608Metric_Pad0.98x0.95mm_HandSolder,,1
SolderJumper_3_Open,AB_3,SolderJumper-3_P1.3mm_Open_RoundedPad1.0x1.5mm_NumberLabels,,1
4.7k,R21,C_0603_1608Metric_Pad1.08x0.95mm_HandSolder,,1
R,R13,C_0603_1608Metric_Pad1.08x0.95mm_HandSolder,,1
SolderJumper_3_Open,SW_1,SolderJumper-3_P1.3mm_Open_RoundedPad1.0x1.5mm_NumberLabels,,1
TestPoint_Alt,46,TestPoint_Pad_D1.5mm,,1
AO3401A,Q6,SOT-23,,1
10K,R30,R_0603_1608Metric_Pad0.98x0.95mm_HandSolder,,1
SolderJumper_3_Open,ALT_B1,SolderJumper-3_P1.3mm_Open_RoundedPad1.0x1.5mm_NumberLabels,,1
TestPoint_Alt,13,TestPoint_Pad_D1.5mm,,1
0,R18,R_0603_1608Metric_Pad0.98x0.95mm_HandSolder,,1
2.2K,R16,R_0603_1608Metric_Pad0.98x0.95mm_HandSolder,,1
C,C7,C_0805_2012Metric_Pad1.18x1.45mm_HandSolder,,1
100nF,C18,C_0603_1608Metric_Pad1.08x0.95mm_HandSolder,,1
0.1uF,C6,C_0805_2012Metric_Pad1.18x1.45mm_HandSolder,,1
C,C8,C_0805_2012Metric_Pad1.18x1.45mm_HandSolder,,1
TestPoint_Alt,11,TestPoint_Pad_D1.5mm,,1
